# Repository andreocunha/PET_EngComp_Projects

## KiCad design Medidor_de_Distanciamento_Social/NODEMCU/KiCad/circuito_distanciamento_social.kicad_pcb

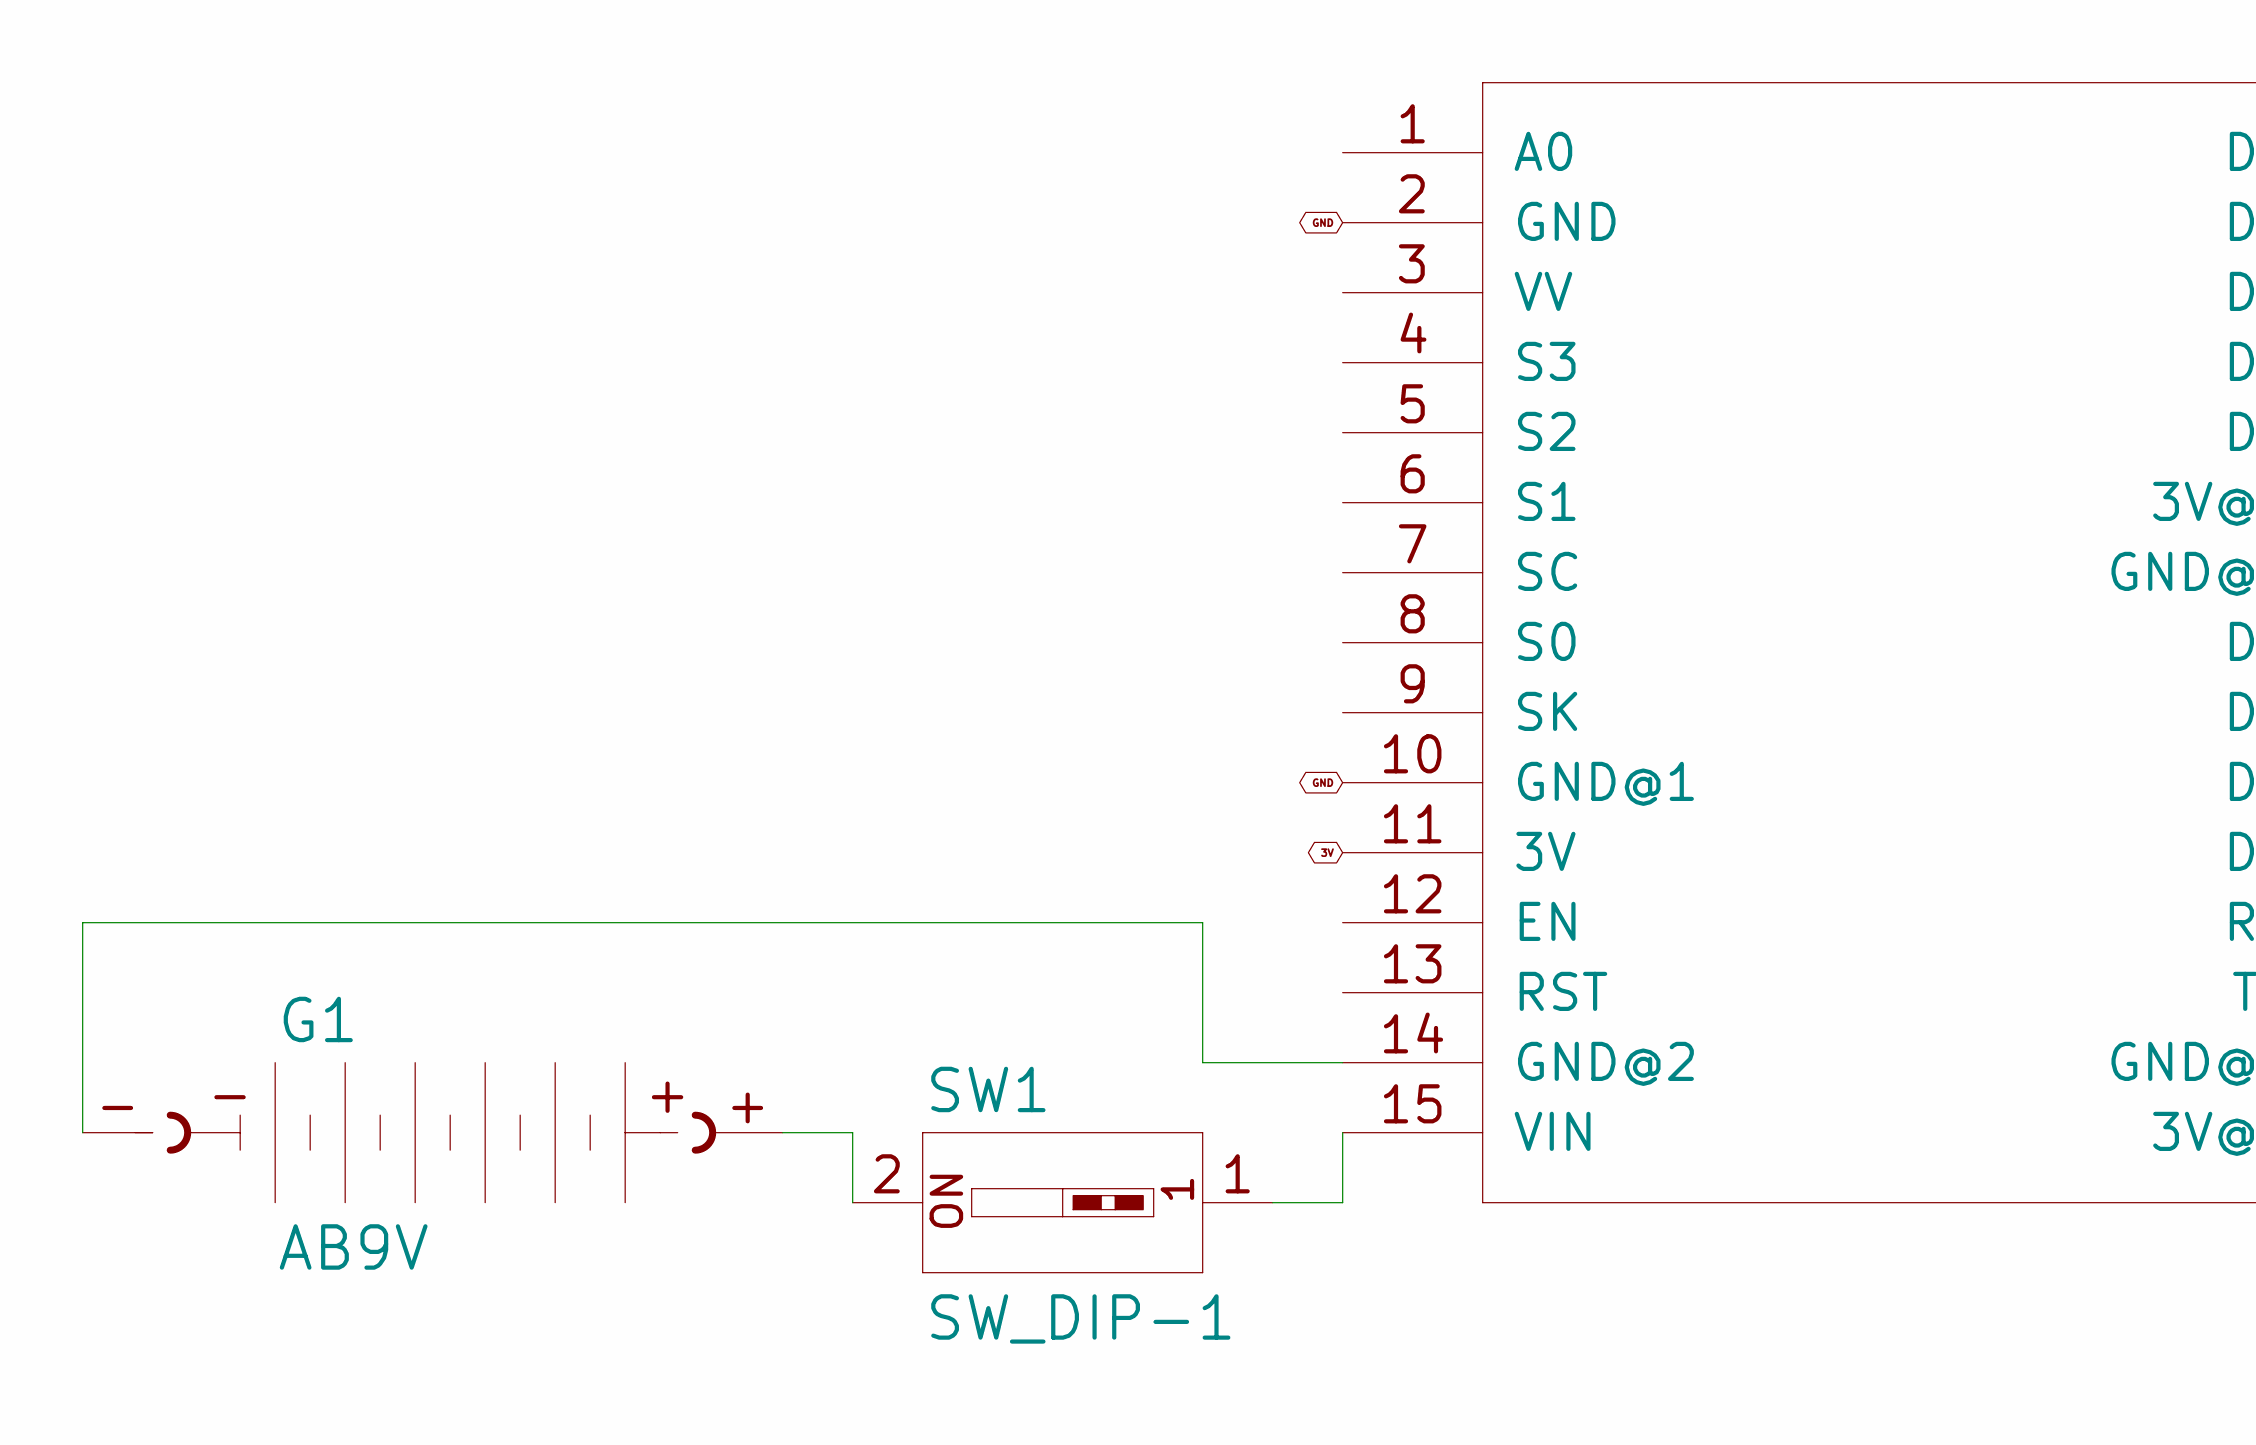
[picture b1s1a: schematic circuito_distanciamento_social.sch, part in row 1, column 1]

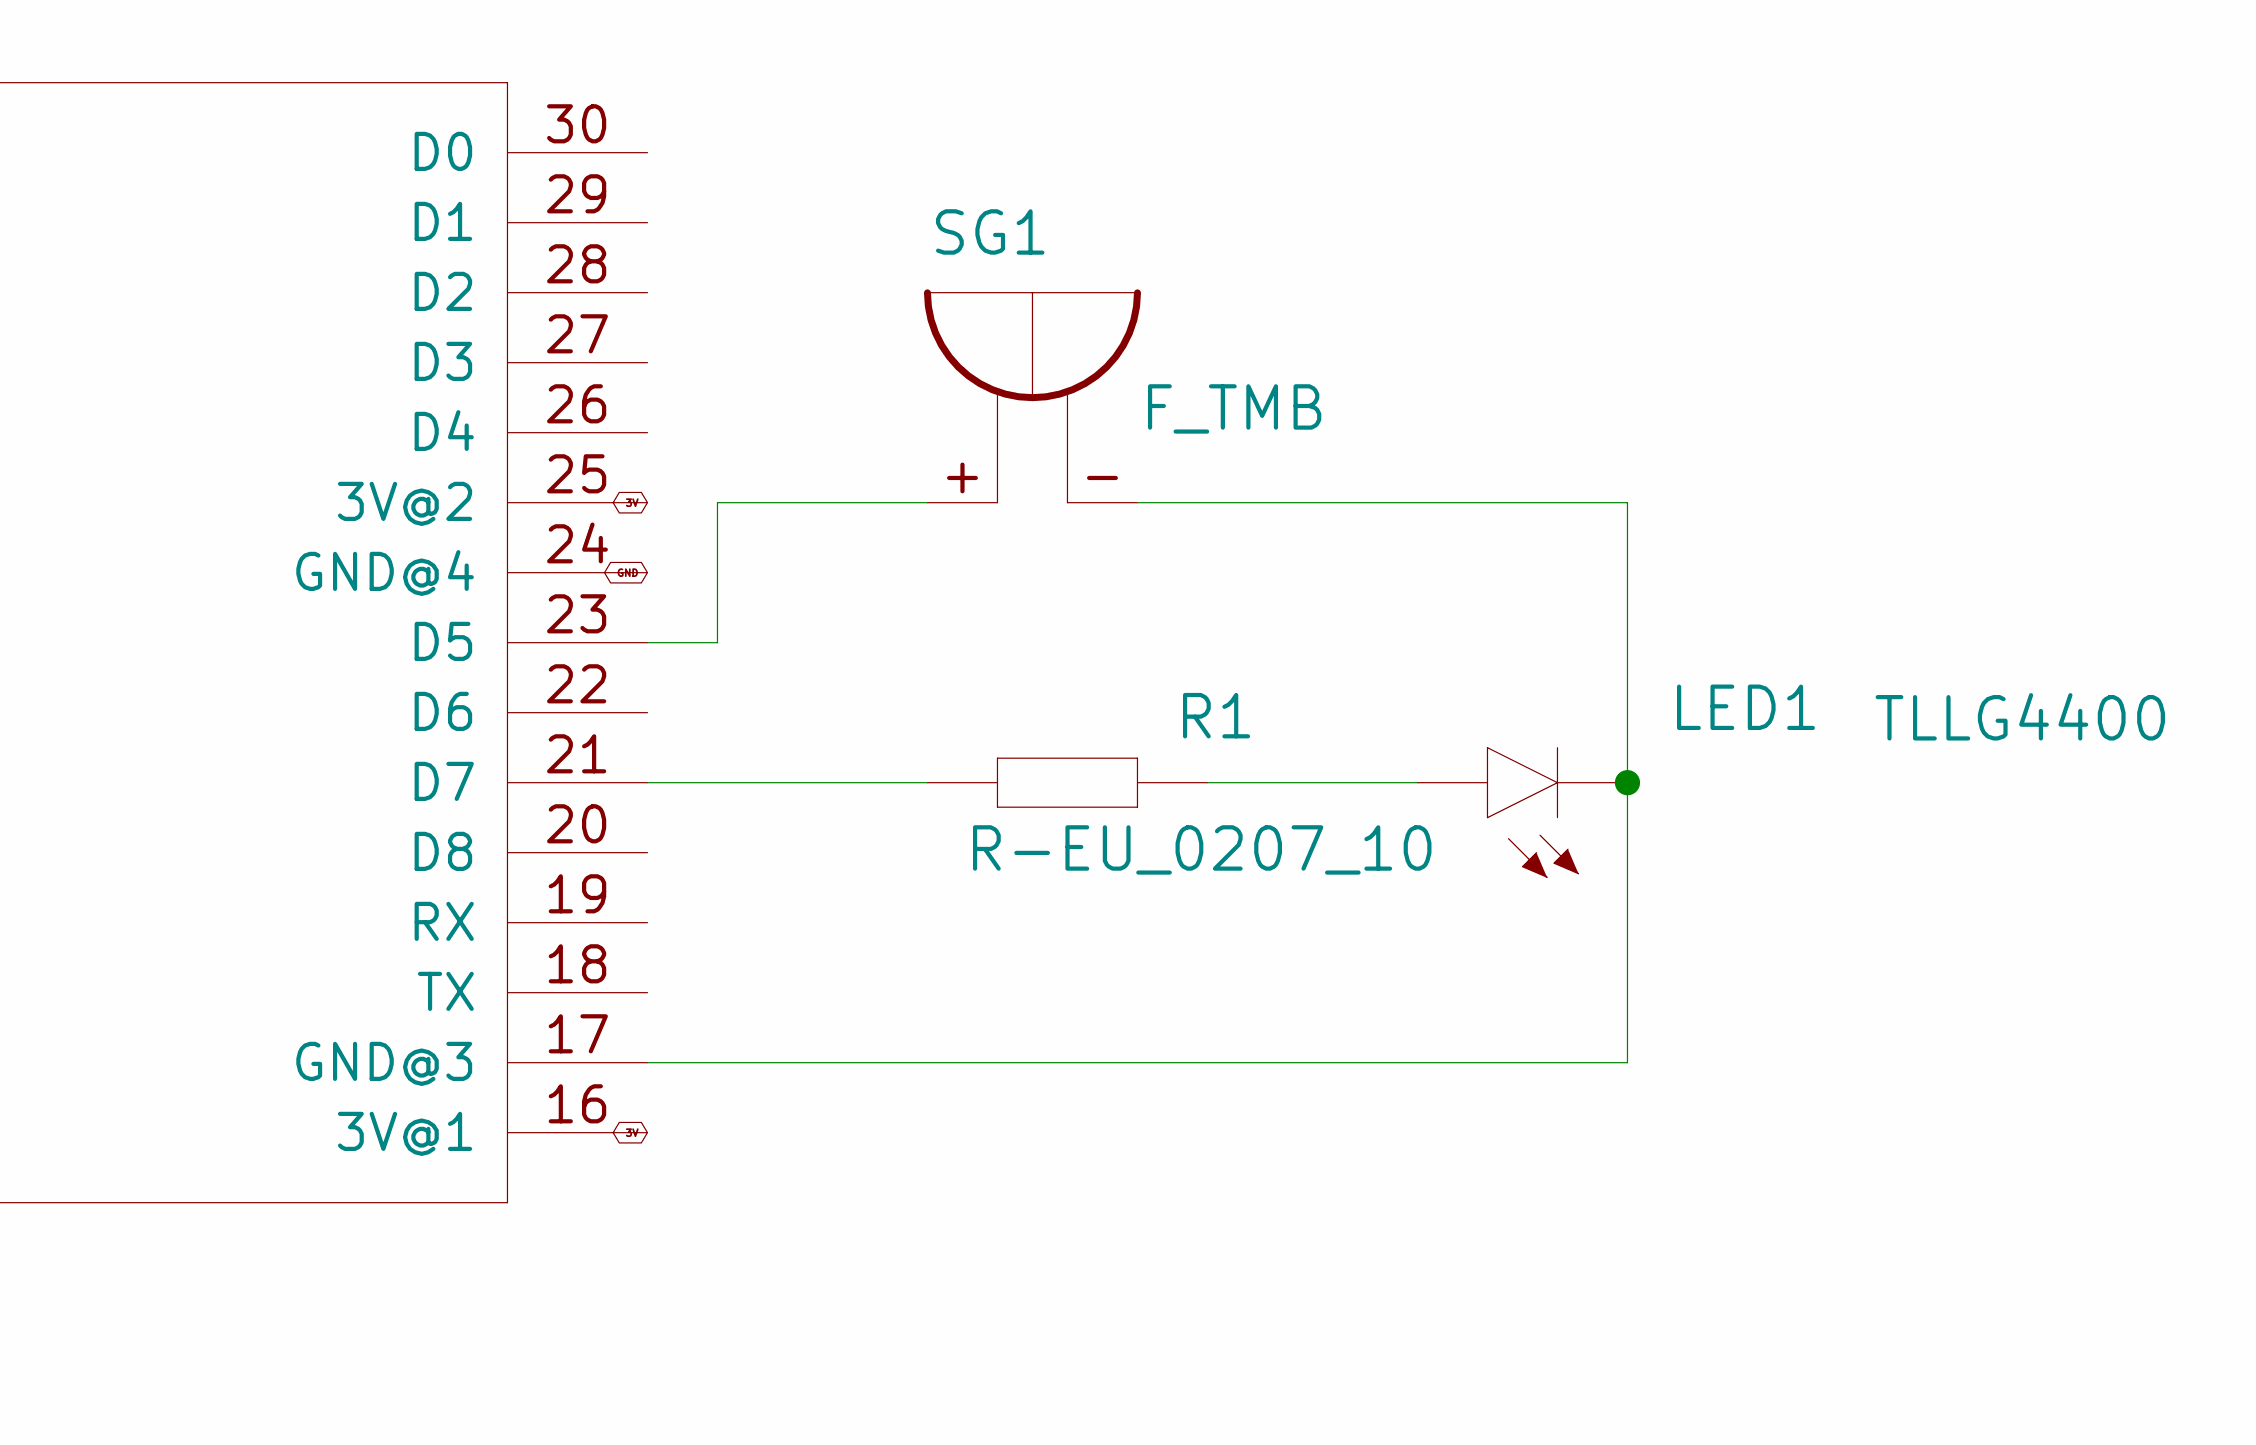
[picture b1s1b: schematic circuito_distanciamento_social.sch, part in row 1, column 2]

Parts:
G1: AB9V
LED1: TLLG4400; LED3MM
R1: R-EU_0207_10; 0207_10
SG1: F_TMB
SW1: SW_DIP-1; EDG-01
U$1: NODEMCU

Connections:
3V: U$1.11 (3V), U$1.16 (3V@1), U$1.25 (3V@2)
GND: U$1.2 (GND), U$1.10 (GND@1), U$1.24 (GND@4)
unnamed: G1.+, SW1.2
unnamed: G1.-, U$1.14 (GND@2)
unnamed: LED1.A, R1.2
unnamed: LED1.K (C), SG1.-, U$1.17 (GND@3)
unnamed: R1.1, U$1.21 (D7)
unnamed: SG1.+, U$1.23 (D5)
unnamed: SW1.1, U$1.15 (VIN)

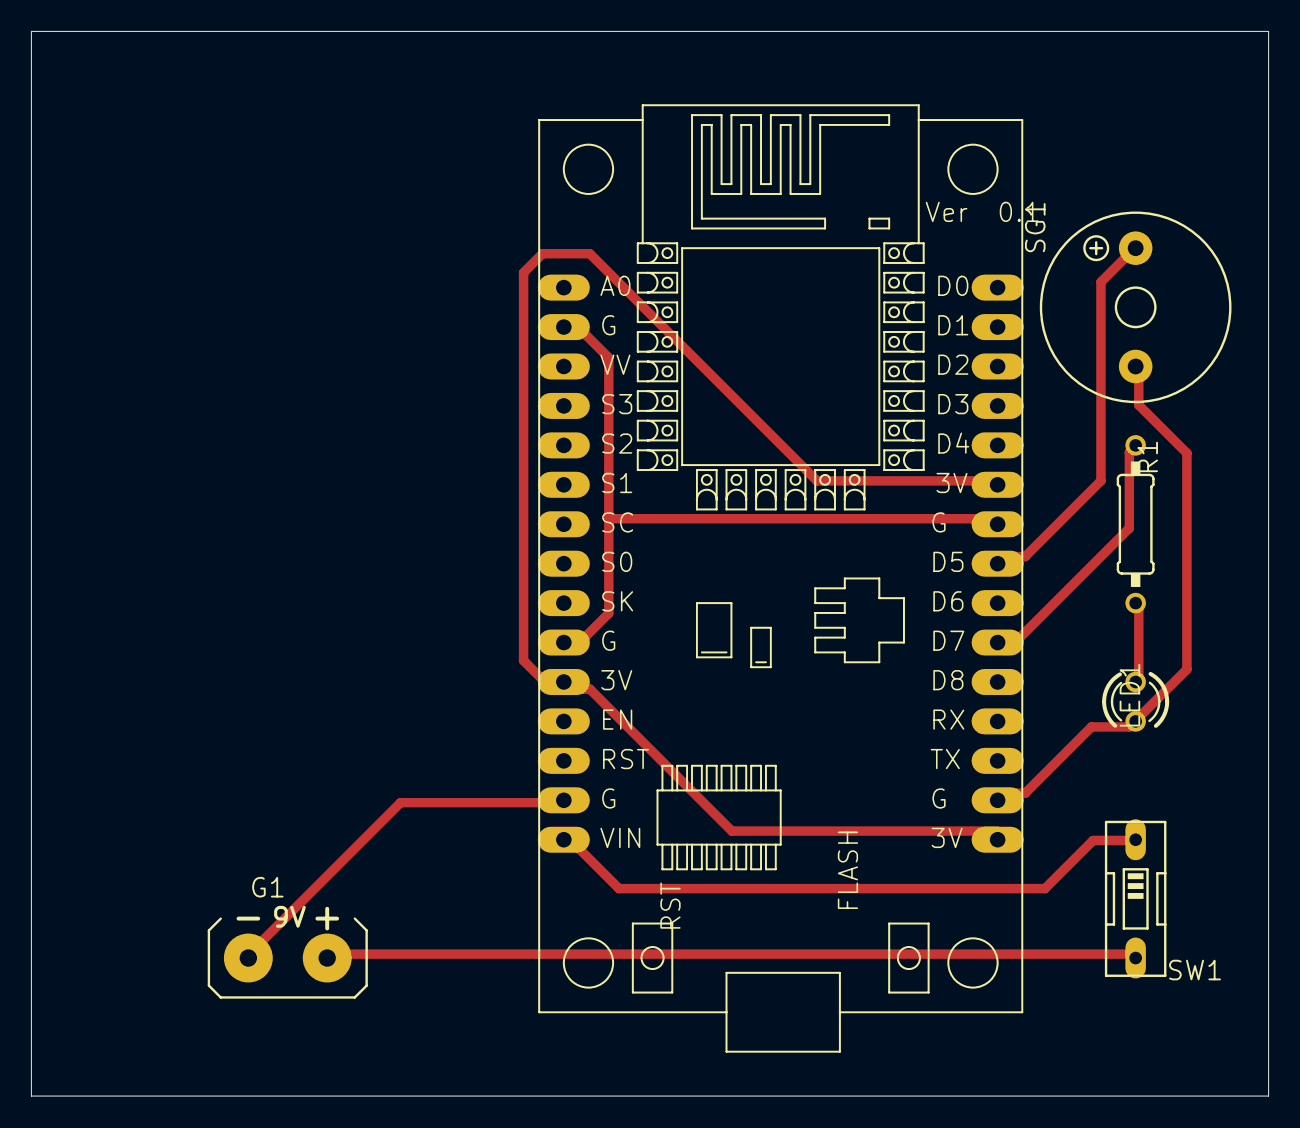
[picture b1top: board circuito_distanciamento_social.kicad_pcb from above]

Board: 2 copper layers, 79.7 x 68.6 mm, 6 parts (0 on the bottom side), 9 nets.

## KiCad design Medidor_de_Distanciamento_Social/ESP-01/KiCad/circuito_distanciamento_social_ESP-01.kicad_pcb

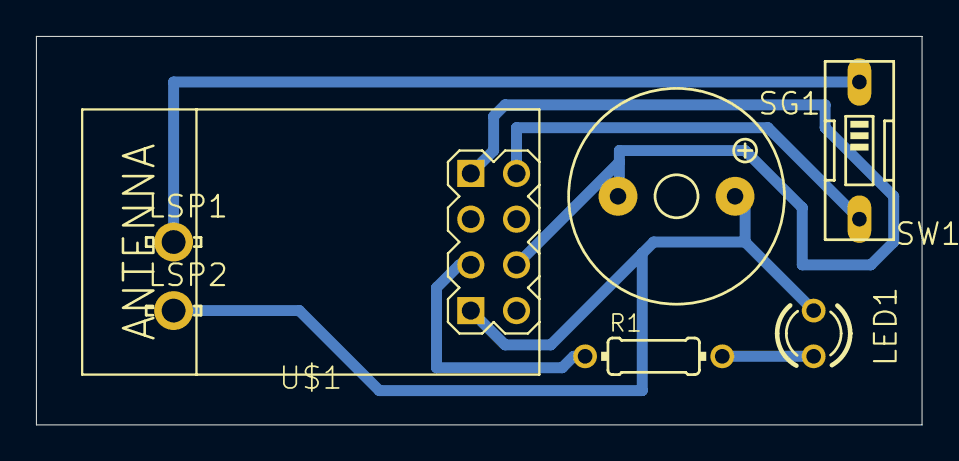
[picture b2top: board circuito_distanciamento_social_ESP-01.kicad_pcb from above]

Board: 2 copper layers, 49.2 x 21.6 mm, 7 parts (0 on the bottom side), 6 nets.

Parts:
LED1: TLLG4400; LED3MM
LSP1, LSP2: LSP13
R1: R-US_0204_7; 0204_7
SG1: F_QMBIII
SW1: SW_DIP-1; EDG-01
U$1: WIRELESS-WIFI-ESP-01

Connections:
unnamed: LED1.A, R1.2
unnamed: LED1.K, LSP2.MP, SG1.+, U$1.A1
unnamed: LSP1.MP, SW1.1
unnamed: R1.1, U$1.B1
unnamed: SG1.-, U$1.B2, U$1.D1
unnamed: SW1.2, U$1.D2

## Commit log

2020-05-30 Medidor de Distanciamento Social
    Circuito criado para manter a segurança entre as pessoas durante o período de pandemia do COVID-19
2020-05-30 Tranca Biométrica com RFID
2020-05-30 Versão 2.0 da tranca biométrica com RFID
2020-05-30 KiCad - Modelo 3D do Circuito
2020-05-30 Imagem do modelo 3D feito no KiCad
2020-08-02 Aumento na velocidade de detecção
2020-08-06 Definindo canal de leitura e busca
2020-08-07 Comentários no código
